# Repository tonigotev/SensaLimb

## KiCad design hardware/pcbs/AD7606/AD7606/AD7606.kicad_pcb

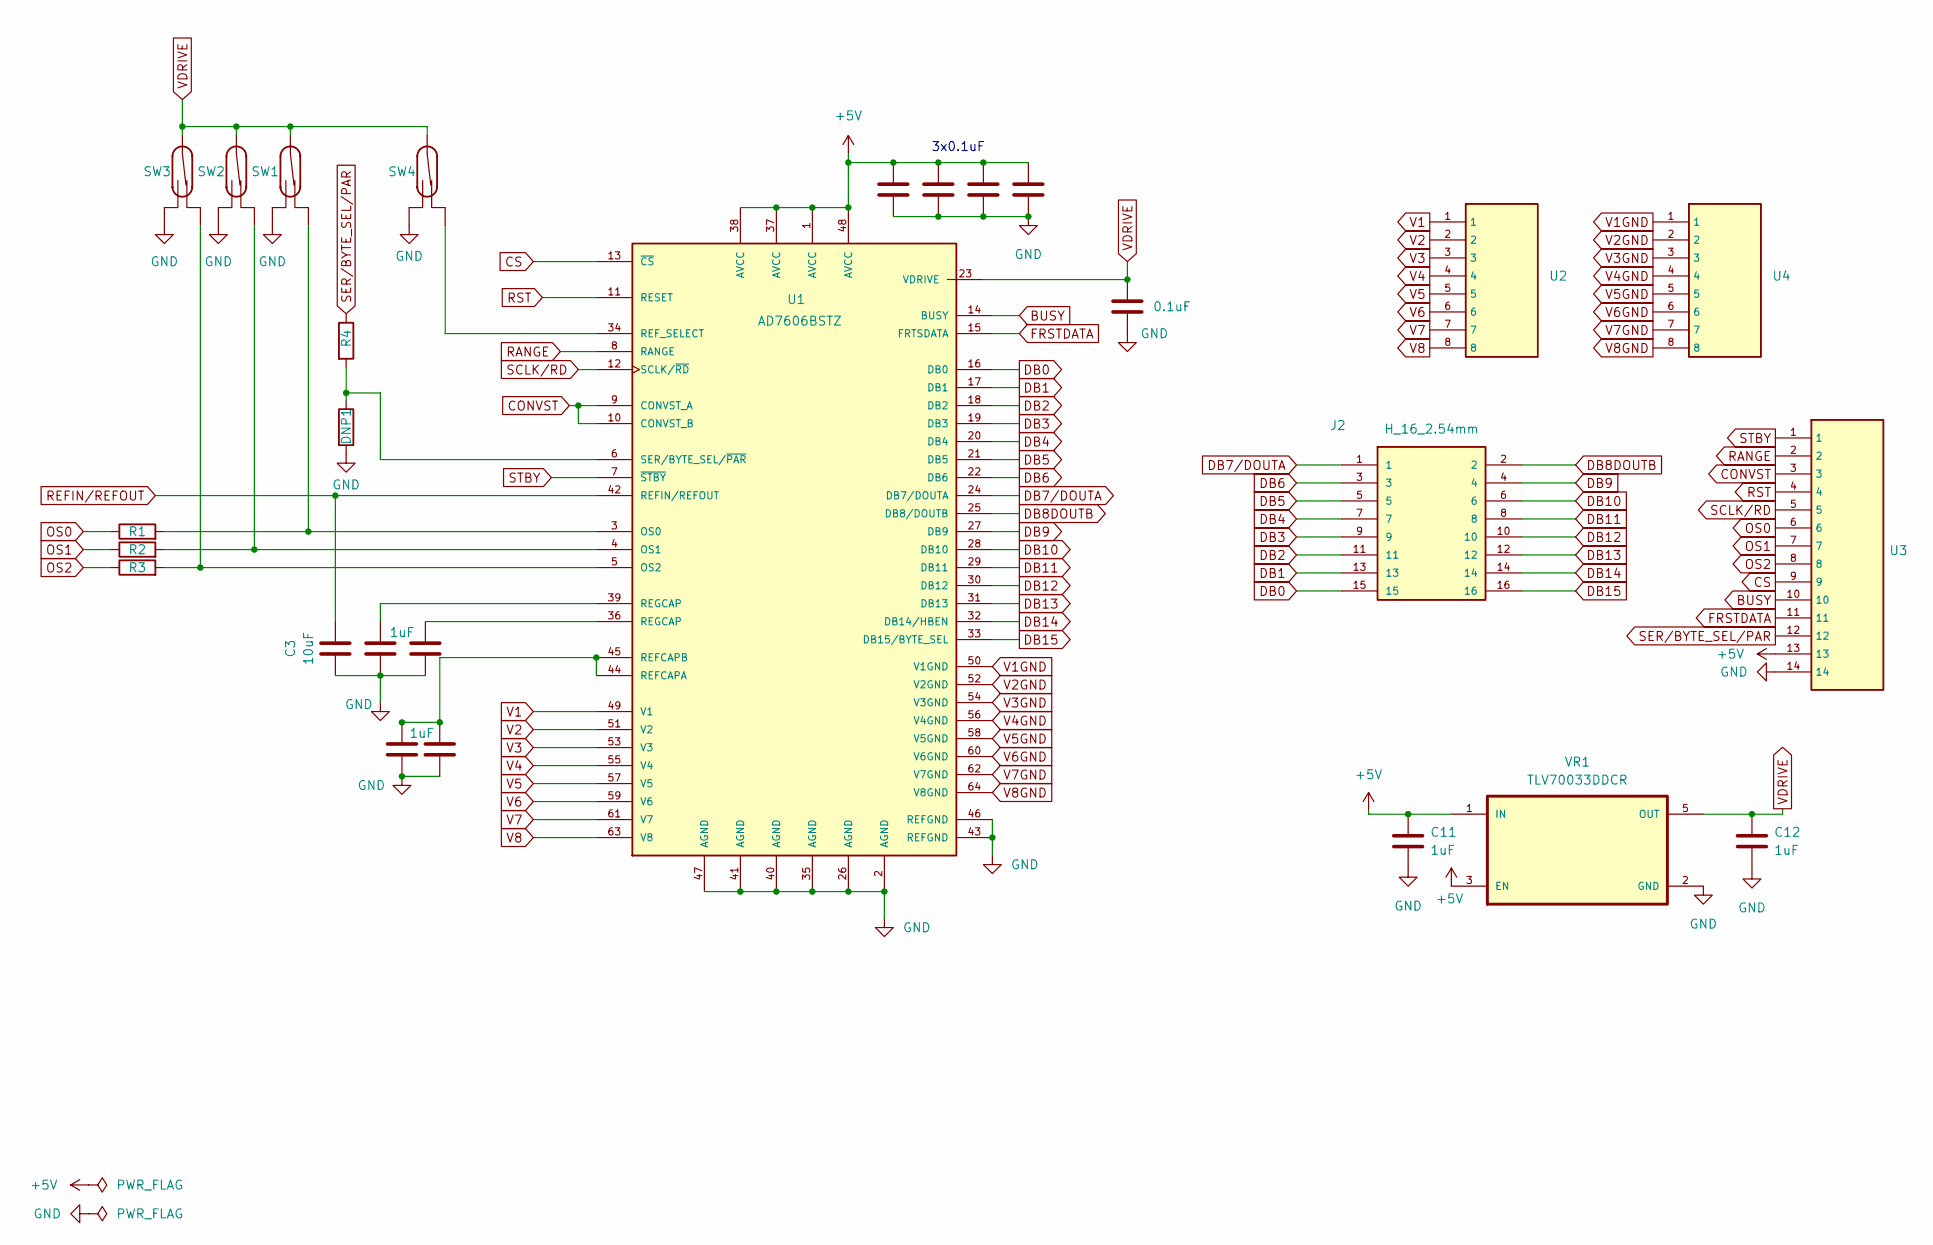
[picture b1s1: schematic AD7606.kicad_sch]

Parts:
C1, C4, C5, C8, C9: 0.1uF; C_0402_1005Metric_Pad0.74x0.62mm_HandSolder
C2, C6, C7, C10, C11, C12: 1uF; C_0402_1005Metric_Pad0.74x0.62mm_HandSolder
C3: 10uF; C_0805_2012Metric_Pad1.18x1.45mm_HandSolder
DNP1: 10-47k; R_0805_2012Metric_Pad1.20x1.40mm_HandSolder
J2: H_16_2.54mm; PinHeader_2x08_P2.54mm_Vertical; PARTREV R
R1, R2, R3: 1k; R_0402_1005Metric_Pad0.72x0.64mm_HandSolder
R4: 1k; R_0805_2012Metric_Pad1.20x1.40mm_HandSolder
SW1, SW2, SW3, SW4: SW_Reed_SPDT; switch1
U1: AD7606BSTZ
U2, U4: PinHeader_1x08_P2.54mm_Vertical
U3: PinHeader_1x14_P2.54mm_Vertical
VR1: TLV70033DDCR

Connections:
+5V: C1.2, C4.2, C8.2, C9.2, C11.1, U1.1 (AVCC), U1.37 (AVCC), U1.38 (AVCC), U1.48 (AVCC), U3.13, VR1.1 (IN), VR1.3 (EN)
BUSY: U1.14 (BUSY), U3.10
CONVST: U1.9 (CONVST_A), U1.10 (CONVST_B), U3.3
CS: U1.13 (~CS), U3.9
DB0: J2.15, U1.16 (DB0)
DB1: J2.13, U1.17 (DB1)
DB2: J2.11, U1.18 (DB2)
DB3: J2.9, U1.19 (DB3)
DB4: J2.7, U1.20 (DB4)
DB5: J2.5, U1.21 (DB5)
DB6: J2.3, U1.22 (DB6)
DB7/DOUTA: J2.1, U1.24 (DB7/DOUTA)
DB8DOUTB: J2.2, U1.25 (DB8/DOUTB)
DB9: J2.4, U1.27 (DB9)
DB10: J2.6, U1.28 (DB10)
DB11: J2.8, U1.29 (DB11)
DB12: J2.10, U1.30 (DB12)
DB13: J2.12, U1.31 (DB13)
DB14: J2.14, U1.32 (DB14/HBEN)
DB15: J2.16, U1.33 (DB15/BYTE_SEL)
FRSTDATA: U1.15 (FRTSDATA), U3.11
GND: C1.1, C2.1, C3.1, C4.1, C5.1, C6.1, C7.2, C8.1, C9.1, C10.2, C11.2, C12.2, DNP1.2, SW1.3, SW2.3, SW3.3, SW4.3, U1.2 (AGND), U1.26 (AGND), U1.35 (AGND), U1.40 (AGND), U1.41 (AGND), U1.43 (REFGND), U1.46 (REFGND), U1.47 (AGND), U3.14, VR1.2 (GND)
unnamed: C2.2, U1.36 (REGCAP)
unnamed: C6.2, U1.39 (REGCAP)
unnamed: R1.2, SW1.1, U1.3 (OS0)
unnamed: R2.2, SW2.1, U1.4 (OS1)
unnamed: R3.2, SW3.1, U1.5 (OS2)
unnamed: C7.1, C10.1, U1.44 (REFCAPA), U1.45 (REFCAPB)
unnamed: SW4.1, U1.34 (REF_SELECT)
unnamed: DNP1.1, R4.2, U1.6 (SER/BYTE_SEL/~PAR)
OS0: R1.1, U3.6
OS1: R2.1, U3.7
OS2: R3.1, U3.8
RANGE: U1.8 (RANGE), U3.2
REFIN/REFOUT: C3.2, U1.42 (REFIN/REFOUT)
RST: U1.11 (RESET), U3.4
SCLK/RD: U1.12 (SCLK/~RD), U3.5
SER/BYTE_SEL/PAR: R4.1, U3.12
STBY: U1.7 (~STBY), U3.1
V1: U1.49 (V1), U2.1
V1GND: U1.50 (V1GND), U4.1
V2: U1.51 (V2), U2.2
V2GND: U1.52 (V2GND), U4.2
V3: U1.53 (V3), U2.3
V3GND: U1.54 (V3GND), U4.3
V4: U1.55 (V4), U2.4
V4GND: U1.56 (V4GND), U4.4
V5: U1.57 (V5), U2.5
V5GND: U1.58 (V5GND), U4.5
V6: U1.59 (V6), U2.6
V6GND: U1.60 (V6GND), U4.6
V7: U1.61 (V7), U2.7
V7GND: U1.62 (V7GND), U4.7
V8: U1.63 (V8), U2.8
V8GND: U1.64 (V8GND), U4.8
VDRIVE: C5.2, C12.1, SW1.2, SW2.2, SW3.2, SW4.2, U1.23 (VDRIVE), VR1.5 (OUT)

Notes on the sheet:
3x0.1uF

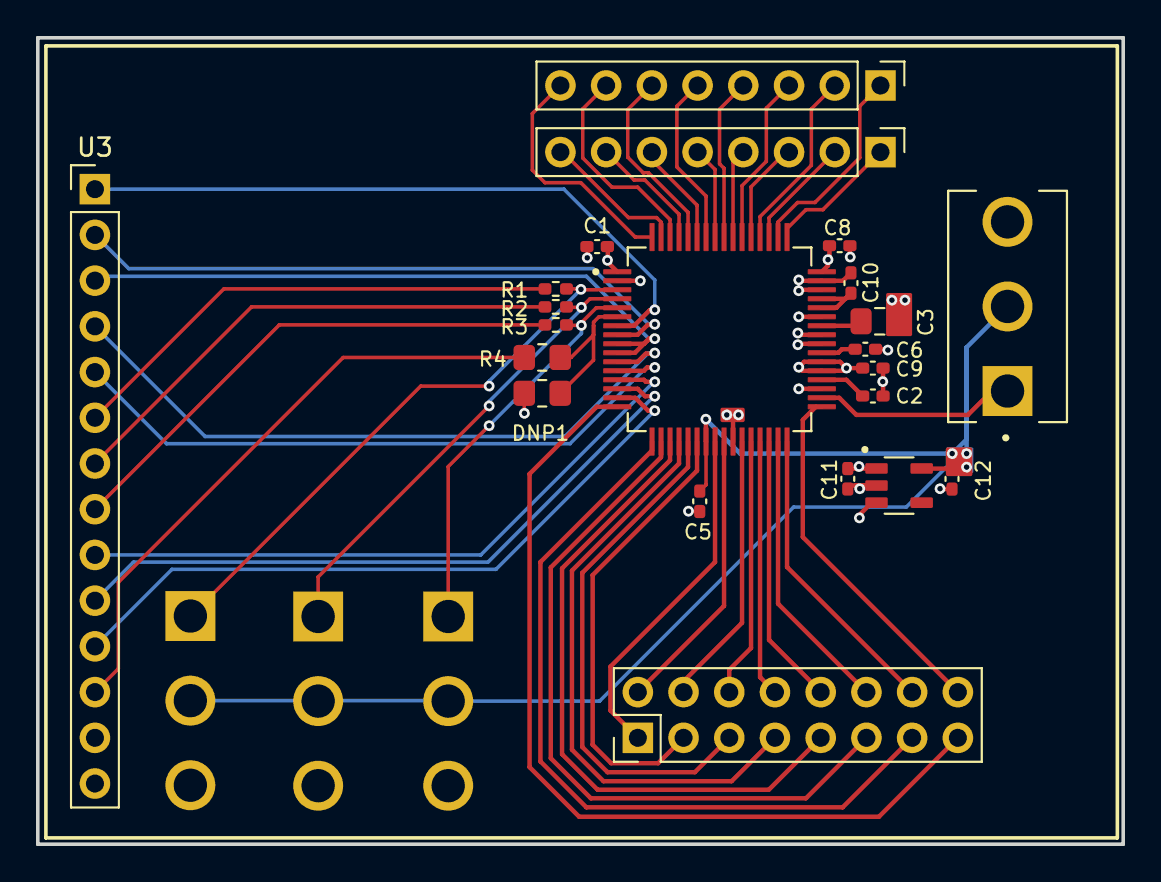
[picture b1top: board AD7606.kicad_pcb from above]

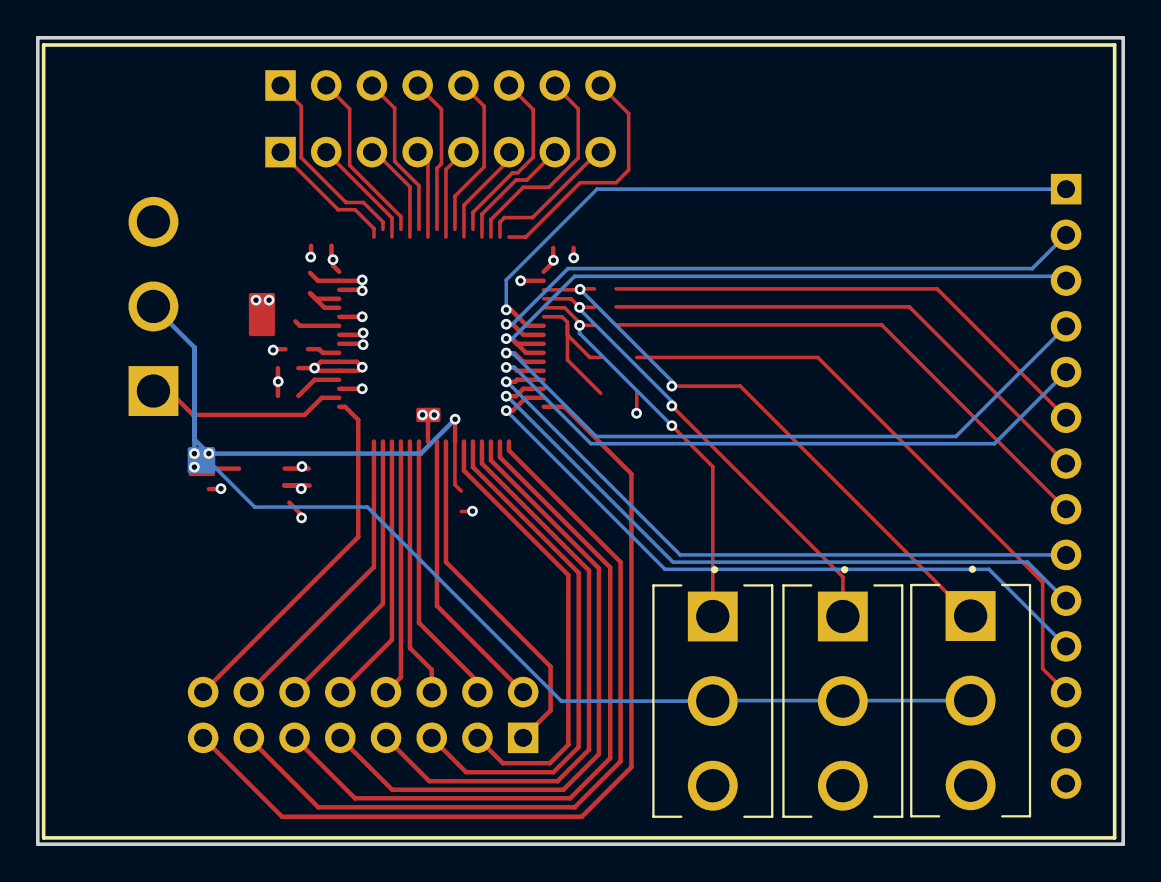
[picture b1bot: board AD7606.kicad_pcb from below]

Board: 4 copper layers, 60.3 x 44.8 mm, 25 parts (3 on the bottom side), 56 nets.

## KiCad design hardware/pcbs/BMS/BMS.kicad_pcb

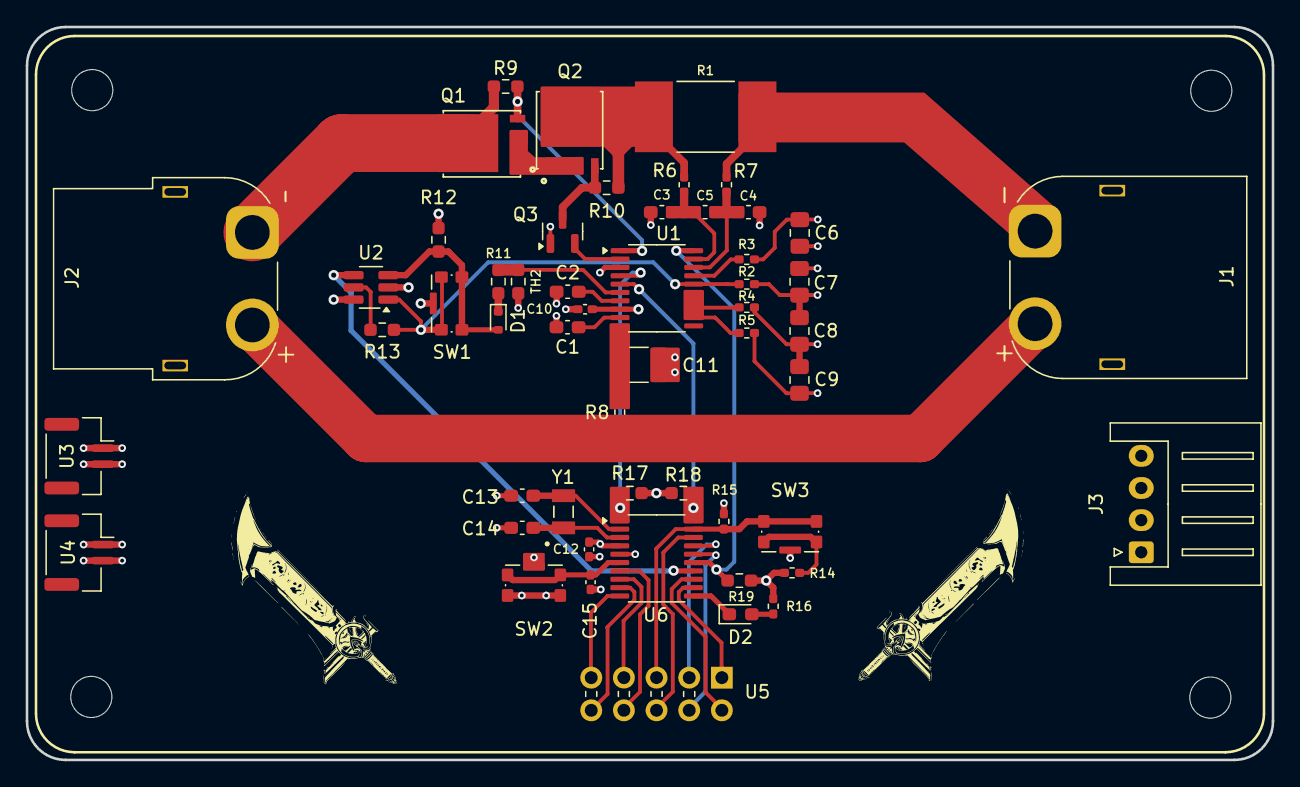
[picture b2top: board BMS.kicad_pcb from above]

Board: 4 copper layers, 96.9 x 57.0 mm, 57 parts (0 on the bottom side), 45 nets.

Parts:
C1, C2: 1uF; C_0603_1608Metric_Pad1.08x0.95mm_HandSolder
C3, C4, C5: 0.1uF; C_0603_1608Metric_Pad1.08x0.95mm_HandSolder
C6, C7, C8, C9: 1uF; C_0805_2012Metric_Pad1.18x1.45mm_HandSolder
C10: 4.7pF; C_0402_1005Metric_Pad0.74x0.62mm_HandSolder
C11: 10uF; C_1210_3225Metric_Pad1.33x2.70mm_HandSolder
C12: 100nF; C_0402_1005Metric_Pad0.74x0.62mm_HandSolder
C13, C14: 12pF; C_0603_1608Metric_Pad1.08x0.95mm_HandSolder
C15: 0.1uF; C_0402_1005Metric_Pad0.74x0.62mm_HandSolder
D1: 1N4148WT; D_SOD-523
D2: BLUE; D_0603_1608Metric_Pad1.05x0.95mm_HandSolder
H1, H2, H3, H4: MountingHole; MountingHole_3.2mm_M3_DIN965
J1: XT60-M; AMASS_XT60PW-M_1x02_P7.20mm_Horizontal
J2: XT60-F; AMASS_XT60PW-F_1x02_P7.20mm_Horizontal
J3: 4-1971800-1; JST_XH_S4B-XH-A_1x04_P2.50mm_Horizontal
Q1, Q2: BSC014N04LSIATMA1; TRANS_BSC014N04LSIATMA1
Q3: BSS84; SOT-23
R1: R; R_3920
R2, R3, R4, R5, R6, R7, R8: 100; R_0402_1005Metric_Pad0.72x0.64mm_HandSolder
R9, R10: 1M; R_0603_1608Metric_Pad0.98x0.95mm_HandSolder
R11, R13: 10k; R_0603_1608Metric_Pad0.98x0.95mm_HandSolder
R12: 47k; R_0603_1608Metric_Pad0.98x0.95mm_HandSolder
R14: 330; R_0402_1005Metric_Pad0.72x0.64mm_HandSolder
R15, R16: 10k; R_0402_1005Metric_Pad0.72x0.64mm_HandSolder
R17, R18, R19: 4.7k; R_0603_1608Metric_Pad0.98x0.95mm_HandSolder
SW1, SW2, SW3: CK_KMS2xxG; SW_SPST_CK_KMS2xxG
TH2: Thermistor_NTC; R_0603_1608Metric_Pad0.98x0.95mm_HandSolder
U1: BQ76920PW; TSSOP-20_4.4x6.5mm_P0.65mm
U2: SN74LVC1T45DCK; SOT-23-6_Handsoldering
U3, U4: JST_GH_SM02B-GHS-TB_1x02-1MP_P1.25mm_Horizontal
U5: PinHeader_2x05_P2.54mm_Horizontal
U6: STM32C011F6Px; TSSOP-20_4.4x6.5mm_P0.65mm
Y1: Crystal; NX3215SA-32.768K-STD-MUA-8

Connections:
+3.3V: C10.2, C12.1, R14.1, R16.2, R17.1, R18.1, R19.1, U1.8 (REGOUT), U2.6 (VCCB), U6.4 (VDD)
/BMS_GND: J2.1, Q1.3 (D), R9.1, U3.1, U4.1
ALERT: R19.2, U1.20 (ALERT), U6.15 (PA8)
unnamed: C6.2, J3.4, R3.2
unnamed: C7.1, C8.2, J3.3, R2.2
unnamed: C8.1, C9.2, J3.2, R4.2
unnamed: C9.1, J3.1, R5.2
unnamed: D1.2 (A), R12.1, SW1.2, U2.3 (A)
unnamed: D1.1 (K), R11.2
unnamed: D2.2 (A), R16.1
unnamed: D2.1 (K), U6.11 (PA4)
unnamed: Q1.1 (G), R9.2, U1.1 (DSG)
unnamed: Q1.2 (S), Q2.2 (S)
unnamed: Q2.3 (D), R1.1, R6.1, R10.1
unnamed: Q2.1 (G), Q3.3 (D), R10.2
unnamed: Q3.2 (S), U1.2 (CHG)
unnamed: R14.2, SW3.1
unnamed: C11.2, R8.1, U1.10 (BAT)
unnamed: C2.2, U1.7 (CAP1)
unnamed: C1.2, U1.9 (REGSRC)
unnamed: C3.2, C5.1, R6.2, U1.19 (SRN)
unnamed: C4.2, C5.2, R7.2, U1.18 (SRP)
unnamed: R11.1, TH2.2, U1.6 (TS1)
unnamed: R3.1, U1.17 (VC0)
unnamed: R2.1, R13.2, SW1.1, U1.16 (VC1), U2.1 (VCCA)
unnamed: R4.1, R5.1, U1.12 (VC5), U1.13 (VC4), U1.14 (VC3), U1.15 (VC2)
unnamed: R13.1, U2.5 (DIR)
unnamed: C13.1, U6.2 (PC14), Y1.2
unnamed: C14.1, U6.3 (PC15), Y1.1
unnamed: C15.1, SW2.1, U6.6 (PF2)
PA0: U5.8, U6.7 (PA0)
PA1: U5.7, U6.8 (PA1)
PA2: U5.10, U6.9 (PA2)
PA3: U5.9, U6.10 (PA3)
PA5: U5.1, U6.12 (PA5)
PA6: U5.2, U6.13 (PA6)
PA11: U5.4, U6.16 (PA9/PA11)
PA12: U5.3, U6.17 (PA10/PA12)
PA13: U5.6, U6.18 (PA13)
PA14: R15.1, SW3.2, U5.5, U6.19 (PA14)
PACK+: J1.2, J2.2, R8.2, U3.2, U4.2
PACK-: C1.1, C2.1, C3.1, C4.1, C6.1, C7.2, C10.1, C11.1, C12.2, C13.2, C14.2, C15.2, J1.1, Q3.1 (G), R1.2, R7.1, R12.2, R15.2, SW1.SH (B), SW2.2, SW2.SH (B), SW3.SH (B), TH2.1, U1.3 (VSS), U2.2 (GND), U6.5 (VSS)
PWROFF: U2.4 (B), U6.14 (PA7)
SCL: R18.2, U1.5 (SCL), U6.20 (PB6)
SDA: R17.2, U1.4 (SDA), U6.1 (PB7)
